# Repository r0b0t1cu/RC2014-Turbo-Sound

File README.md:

# RC2014 Turbo Sound

An original dual AY/YM TurboSound board for RC bus systems and compatible Z80 computers. The design combines two AY-compatible sound chips, a stereo audio output, selectable address decoding, and clock-source/divider options.

The schematic and PCB were developed for this project. The compact DIP layout was designed to fit within the RC bus width while keeping the board height acceptable.

## Features

- Two AY-3-8910 or YM2149-compatible sound chips.
- TurboSound chip selection through the board's `$F8` / `$F9` soft-select commands.
- Selectable MSX-style 8-bit I/O and ZX Spectrum-style 16-bit I/O address decoding.
- Onboard oscillator or RC bus clock, with selectable clock division.
- Stereo audio output.
- Two-row J1 RC bus connector footprint; one row provides the electrical connection and the additional row supports RC bus fit and mechanical stability.

---

*Click the image above to watch the project demonstration on YouTube.*

## Compatibility

Designed for RC bus / RC2014 systems, including compatible SC7xx RCBus computers. It can also be used with a ZX Spectrum through an appropriate adapter and matching software configuration.

TSPLAYER is the companion CP/M/RomWBW PT3 player: [r0b0t1cu/TSPLAYER](https://github.com/r0b0t1cu/TSPLAYER). TSPLAYER controls the two AY chips through the board's shared AY port pair and `$F8` / `$F9` selection commands. Its eight-LED level display uses the separate RCBus Digital I/O module at port 0.

## Design and documentation files

| File | Description |
| --- | --- |
| [`RC2014-Turbo-Sound-KiCad/`](RC2014-Turbo-Sound-KiCad/) | Editable KiCad schematic, PCB, project, and custom RC bus footprints |
| [`docs/schematic.pdf`](docs/schematic.pdf) | Schematic PDF |
| [`docs/images/turbosound-board-photo.jpg`](docs/images/turbosound-board-photo.jpg) | Photograph of the assembled board |
| [`docs/images/board-top.png`](docs/images/board-top.png) | Top-side PCB render |
| [`docs/images/board-bottom.png`](docs/images/board-bottom.png) | Bottom-side PCB render and silkscreen jumper legend |
| [`docs/ibom.html`](docs/ibom.html) | Interactive bill of materials |
| [`docs/JUMPER_SETTINGS.md`](docs/JUMPER_SETTINGS.md) | Address, mode, clock, and connector notes |

## Fabrication files

Generated files are in [`production/2026-11-07-21-17-36/`](production/2026-11-07-21-17-36/): [BOM](production/2026-11-07-21-17-36/RC2014-Turbo-Sound.kicad_pcb_bom.csv), [component positions](production/2026-11-07-21-17-36/RC2014-Turbo-Sound.kicad_pcb_positions.csv), [IPC netlist](production/2026-11-07-21-17-36/RC2014-Turbo-Sound.kicad_pcb_netlist.ipc), and [Gerber archive](production/2026-11-07-21-17-36/RC2014-Turbo-Sound.kicad_pcb_gerber.zip).

If you enjoy my projects and would like to support my work, you can do so through PCBWay. You can also order the PCBs for this project directly from the link below. Every bit of support is appreciated!

<p>
  
</p>

## Design inspiration and credits

The design was inspired by the TurboSound interface concepts in [KTS](https://github.com/konkotgit/KTS) and the AY/YM sound-board work in [electrified/rc2014-ym2149](https://github.com/electrified/rc2014-ym2149). Those projects remain the work of their respective authors. The schematic implementation and PCB layout in this repository were developed for this board.

## License

Hardware design files are released under the **CERN Open Hardware Licence Version 2 – Permissive (CERN-OHL-P-2.0)**. See [LICENSE](LICENSE). The license permits use, modification, manufacture, and sale, subject to its terms and notices.

Copyright © 2025-2026 r0b0t1cu.

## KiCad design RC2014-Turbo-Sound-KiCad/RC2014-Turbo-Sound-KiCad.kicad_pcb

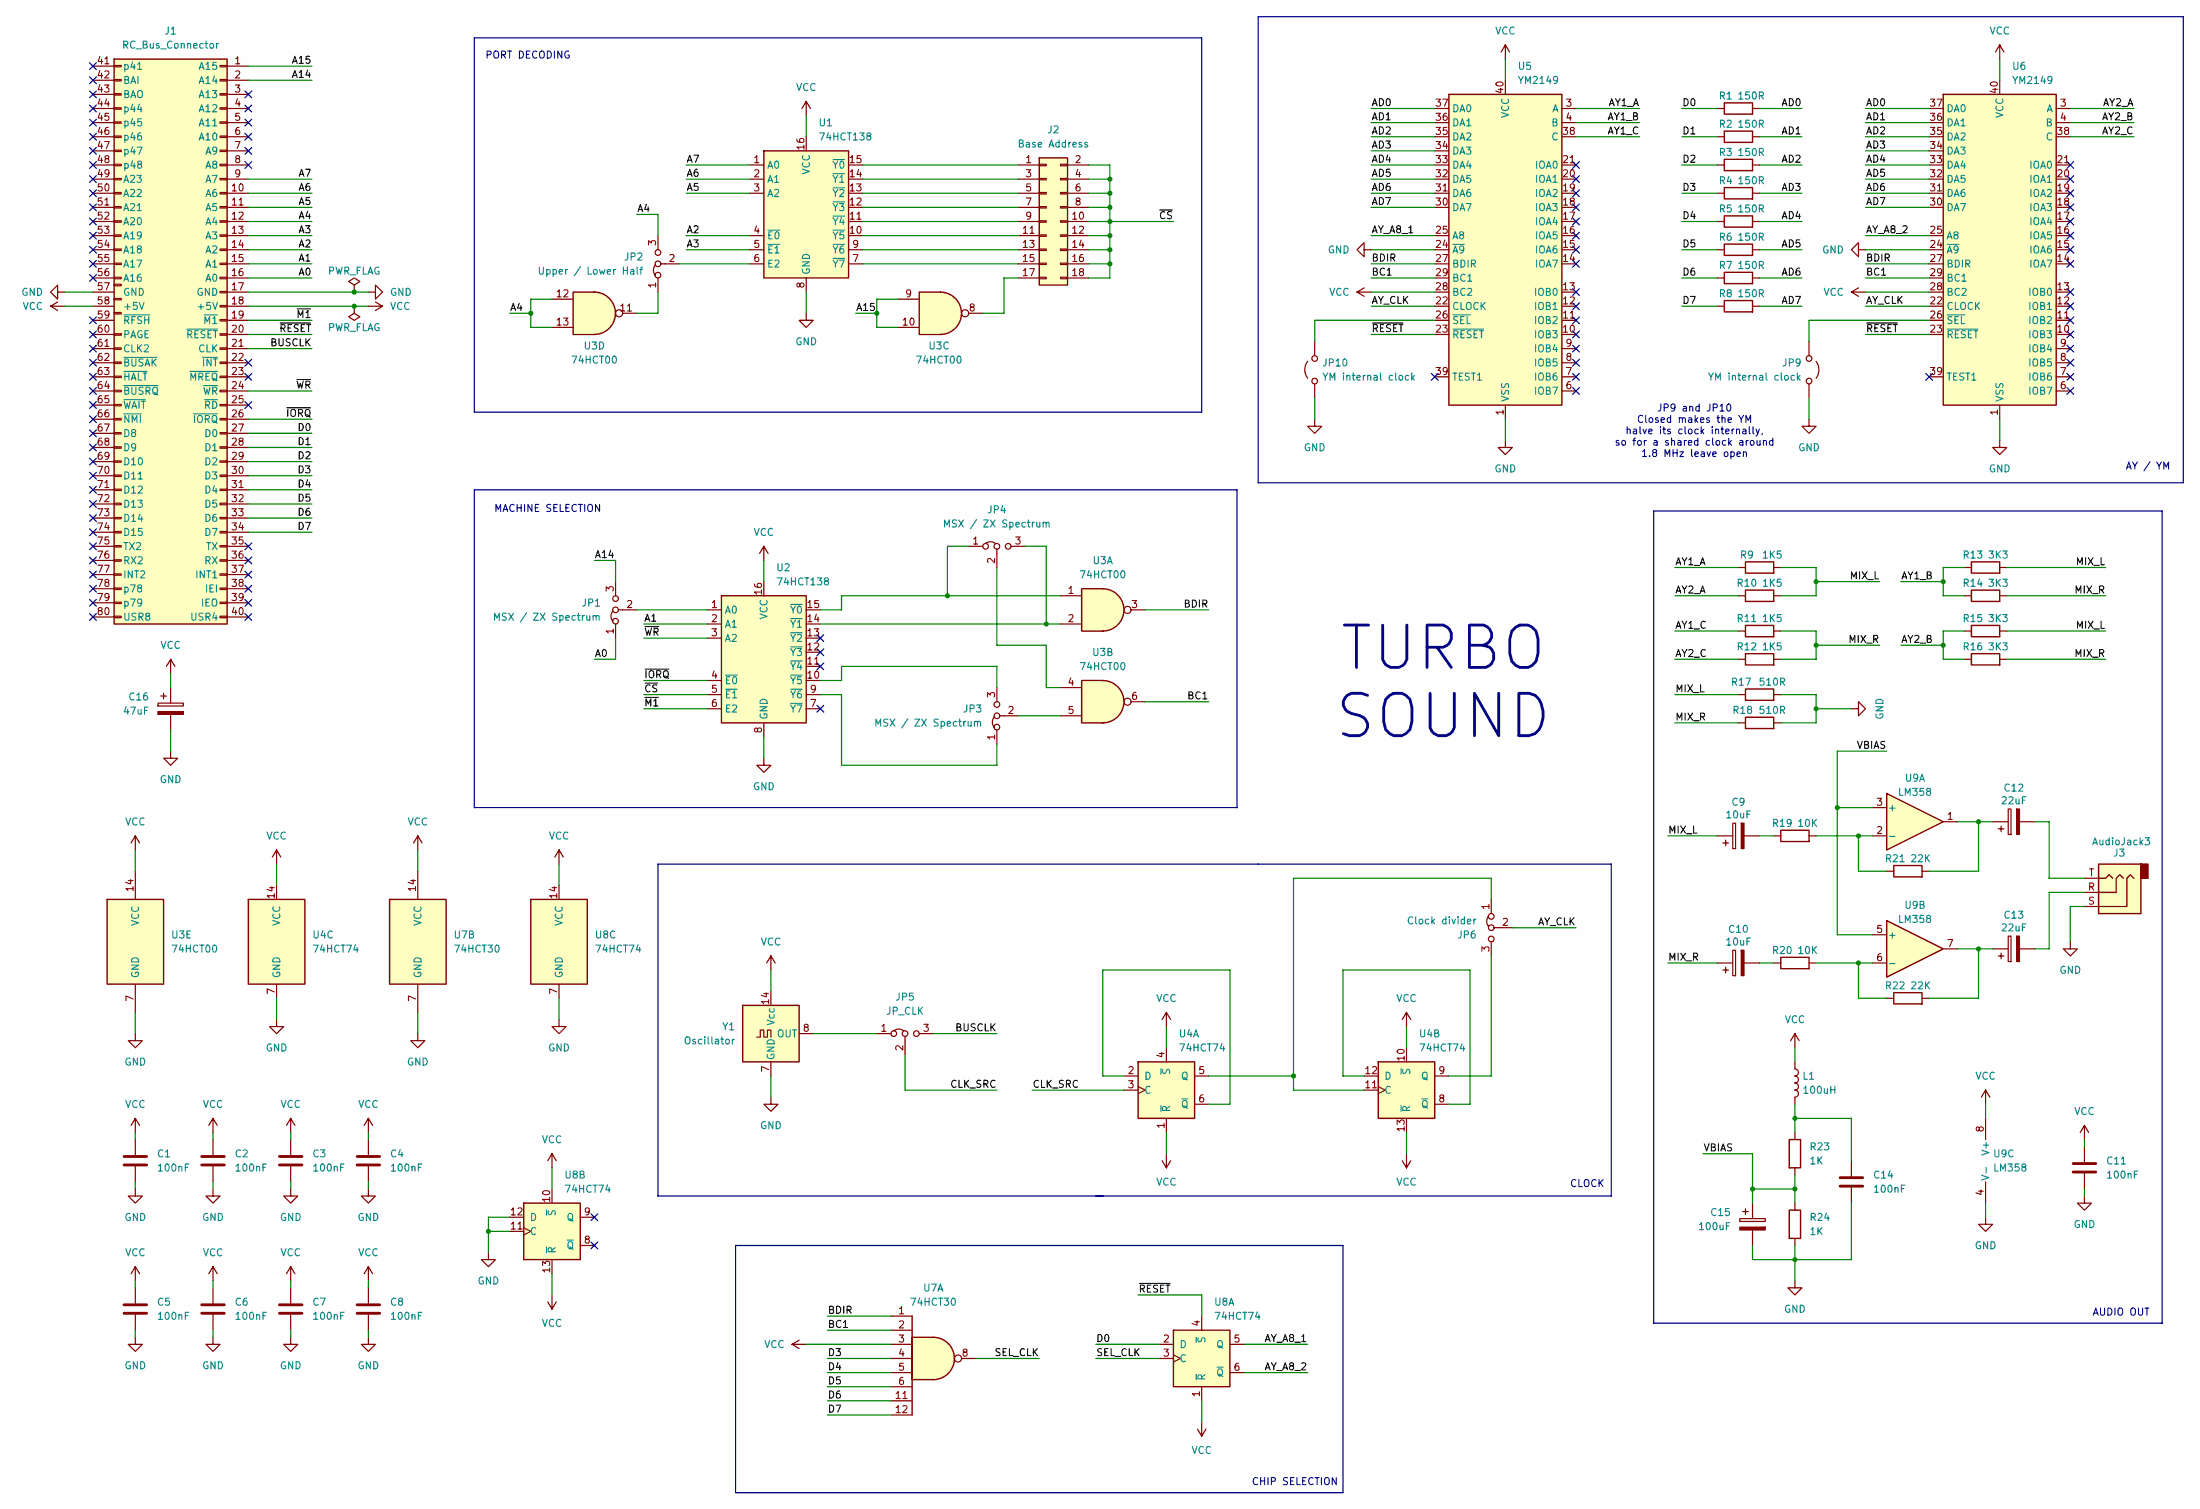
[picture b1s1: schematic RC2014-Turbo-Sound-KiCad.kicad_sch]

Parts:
C1, C2, C3, C4, C5, C6, C7, C8, C11, C14: 100nF; C_Disc_D5.0mm_W2.5mm_P2.50mm
C9, C10: 10uF; CP_Radial_D5.0mm_P2.50mm
C12, C13: 22uF; CP_Radial_D5.0mm_P2.50mm
C15: 100uF; CP_Radial_D5.0mm_P2.50mm
C16: 47uF; CP_Radial_D5.0mm_P2.50mm
J1: RC_Bus_Connector; PinHeader_2x40_P2.54mm_Vertical
J2: Base Address; PinHeader_2x09_P2.54mm_Vertical
J3: AudioJack3; Jack_3.5mm_CUI_SJ1-3525N_Horizontal
JP1, JP3, JP4: MSX / ZX Spectrum; PinHeader_1x03_P2.54mm_Vertical
JP2: Upper / Lower Half; PinHeader_1x03_P2.54mm_Vertical
JP5: JP_CLK; PinHeader_1x03_P2.54mm_Vertical
JP6: Clock divider; PinHeader_1x03_P2.54mm_Vertical
JP9, JP10: YM internal clock; PinHeader_1x02_P2.54mm_Vertical
L1: 100uH; L_Radial_D8.7mm_P5.00mm_Fastron_07HCP
R1, R2, R3, R4, R5, R6, R7, R8: 150R; R_Axial_DIN0207_L6.3mm_D2.5mm_P7.62mm_Horizontal
R9, R10, R11, R12: 1K5; R_Axial_DIN0207_L6.3mm_D2.5mm_P7.62mm_Horizontal
R13, R14, R15, R16: 3K3; R_Axial_DIN0207_L6.3mm_D2.5mm_P7.62mm_Horizontal
R17, R18: 510R; R_Axial_DIN0207_L6.3mm_D2.5mm_P7.62mm_Horizontal
R19, R20: 10K; R_Axial_DIN0207_L6.3mm_D2.5mm_P7.62mm_Horizontal
R21, R22: 22K; R_Axial_DIN0207_L6.3mm_D2.5mm_P7.62mm_Horizontal
R23, R24: 1K; R_Axial_DIN0207_L6.3mm_D2.5mm_P7.62mm_Horizontal
U1, U2: 74HCT138; DIP-16_W7.62mm_Socket_LongPads
U3: 74HCT00; DIP-14_W7.62mm_Socket_LongPads
U4, U8: 74HCT74; DIP-14_W7.62mm_Socket_LongPads
U5, U6: YM2149; DIP-40_W15.24mm_Socket_LongPads
U7: 74HCT30; DIP-14_W7.62mm_Socket_LongPads
U9: LM358; DIP-8_W7.62mm_Socket_LongPads
Y1: Oscillator; DIP-14_W7.62mm_Socket_LongPads

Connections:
/A0: J1.16 (A0), JP1.1 (A)
/A1: J1.15 (A1), U2.2 (A1)
/A2: J1.14 (A2), U1.4 (~E0)
/A3: J1.13 (A3), U1.5 (~E1)
/A4: J1.12 (A4), JP2.3 (B), U3.12, U3.13
/A5: J1.11 (A5), U1.3 (A2)
/A6: J1.10 (A6), U1.2 (A1)
/A7: J1.9 (A7), U1.1 (A0)
/A14: J1.2 (A14), JP1.3 (B)
/A15: J1.1 (A15), U3.9, U3.10
/AD0: R1.2, U5.37 (DA0), U6.37 (DA0)
/AD1: R2.2, U5.36 (DA1), U6.36 (DA1)
/AD2: R3.2, U5.35 (DA2), U6.35 (DA2)
/AD3: R4.2, U5.34 (DA3), U6.34 (DA3)
/AD4: R5.2, U5.33 (DA4), U6.33 (DA4)
/AD5: R6.2, U5.32 (DA5), U6.32 (DA5)
/AD6: R7.2, U5.31 (DA6), U6.31 (DA6)
/AD7: R8.2, U5.30 (DA7), U6.30 (DA7)
/AY1_A: R9.1, U5.3 (A)
/AY1_B: R13.1, R14.1, U5.4 (B)
/AY1_C: R11.1, U5.38 (C)
/AY2_A: R10.1, U6.3 (A)
/AY2_B: R15.1, R16.1, U6.4 (B)
/AY2_C: R12.1, U6.38 (C)
/AY_A8_1: U5.25 (A8), U8.5 (Q)
/AY_A8_2: U6.25 (A8), U8.6 (~Q)
/AY_CLK: JP6.2 (C), U5.22 (CLOCK), U6.22 (CLOCK)
/BC1: U3.6, U5.29 (BC1), U6.29 (BC1), U7.2
/BDIR: U3.3, U5.27 (BDIR), U6.27 (BDIR), U7.1
/BUSCLK: J1.21 (CLK), JP5.3 (B)
/CLK_SRC: JP5.2 (C), U4.3 (C)
/D0: J1.27 (D0), R1.1, U8.2 (D)
/D1: J1.28 (D1), R2.1
/D2: J1.29 (D2), R3.1
/D3: J1.30 (D3), R4.1, U7.4
/D4: J1.31 (D4), R5.1, U7.5
/D5: J1.32 (D5), R6.1, U7.6
/D6: J1.33 (D6), R7.1, U7.11
/D7: J1.34 (D7), R8.1, U7.12
/MIX_L: C9.1, R9.2, R10.2, R13.2, R15.2, R17.1
/MIX_R: C10.1, R11.2, R12.2, R14.2, R16.2, R18.1
/SEL_CLK: U7.8, U8.3 (C)
/VBIAS: C15.1, R23.2, R24.1, U9.3 (+), U9.5 (+)
/~CS: J2.2, J2.4, J2.6, J2.8, J2.10, J2.12, J2.14, J2.16, J2.18, U2.5 (~E1)
/~IORQ: J1.26 (~IORQ), U2.4 (~E0)
/~M1: J1.19 (~M1), U2.6 (E2)
/~RESET: J1.20 (~RESET), U5.23 (~RESET), U6.23 (~RESET), U8.4 (~S)
/~WR: J1.24 (~WR), U2.3 (A2)
GND: C1.2, C2.2, C3.2, C4.2, C5.2, C6.2, C7.2, C8.2, C11.2, C14.2, C15.2, C16.2, J1.17 (GND), J1.57 (GND), J3.S, JP9.1 (A), JP10.1 (A), R17.2, R18.2, R24.2, U1.8 (GND), U2.8 (GND), U3.7 (GND), U4.7 (GND), U5.1 (VSS), U5.24 (~A9), U6.1 (VSS), U6.24 (~A9), U7.7 (GND), U8.7 (GND), U8.11 (C), U8.12 (D), U9.4 (V-), Y1.4, Y1.7 (GND)
unnamed: C9.2, R19.1
unnamed: C10.2, R20.1
unnamed: C12.1, R21.2, U9.1
unnamed: C12.2, J3.T, J3.TN
unnamed: C13.1, R22.2, U9.7
unnamed: C13.2, J3.R, J3.RN
unnamed: C14.1, L1.2, R23.1
unnamed: J2.1, U1.15 (~Y0)
unnamed: J2.3, U1.14 (~Y1)
unnamed: J2.5, U1.13 (~Y2)
unnamed: J2.7, U1.12 (~Y3)
unnamed: J2.9, U1.11 (~Y4)
unnamed: J2.11, U1.10 (~Y5)
unnamed: J2.13, U1.9 (~Y6)
unnamed: J2.15, U1.7 (~Y7)
unnamed: J2.17, U3.8
unnamed: JP1.2 (C), U2.1 (A0)
unnamed: JP2.1 (A), U3.11
unnamed: JP2.2 (C), U1.6 (E2)
unnamed: JP3.1 (A), U2.9 (~Y6)
unnamed: JP3.3 (B), U2.10 (~Y5)
unnamed: JP3.2 (C), U3.5
unnamed: JP4.1 (A), U2.15 (~Y0), U3.1
unnamed: JP4.3 (B), U2.14 (~Y1), U3.2
unnamed: JP4.2 (C), U3.4
unnamed: JP5.1 (A), Y1.8 (OUT), Y1.11
unnamed: JP6.1 (A), U4.5 (Q), U4.11 (C)
unnamed: JP6.3 (B), U4.9 (Q)
unnamed: JP9.2 (B), U6.26 (~SEL)
unnamed: JP10.2 (B), U5.26 (~SEL)
unnamed: U4.2 (D), U4.6 (~Q)
unnamed: U4.8 (~Q), U4.12 (D)
unnamed: R19.2, R21.1, U9.2 (-)
unnamed: R20.2, R22.1, U9.6 (-)
VCC: C1.1, C2.1, C3.1, C4.1, C5.1, C6.1, C7.1, C8.1, C11.1, C16.1, J1.18 (+5V), J1.58 (+5V), L1.1, U1.16 (VCC), U2.16 (VCC), U3.14 (VCC), U4.1 (~R), U4.4 (~S), U4.10 (~S), U4.13 (~R), U4.14 (VCC), U5.28 (BC2), U5.40 (VCC), U6.28 (BC2), U6.40 (VCC), U7.3, U7.14 (VCC), U8.1 (~R), U8.10 (~S), U8.13 (~R), U8.14 (VCC), U9.8 (V+), Y1.14 (Vcc)

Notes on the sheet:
AUDIO OUT
AY / YM
PORT DECODING
CHIP SELECTION
TURBO SOUND
JP9 and JP10 Closed makes the YM halve its clock internally, so for a shared clock around 1.8 MHz leave open
MACHINE SELECTION
CLOCK

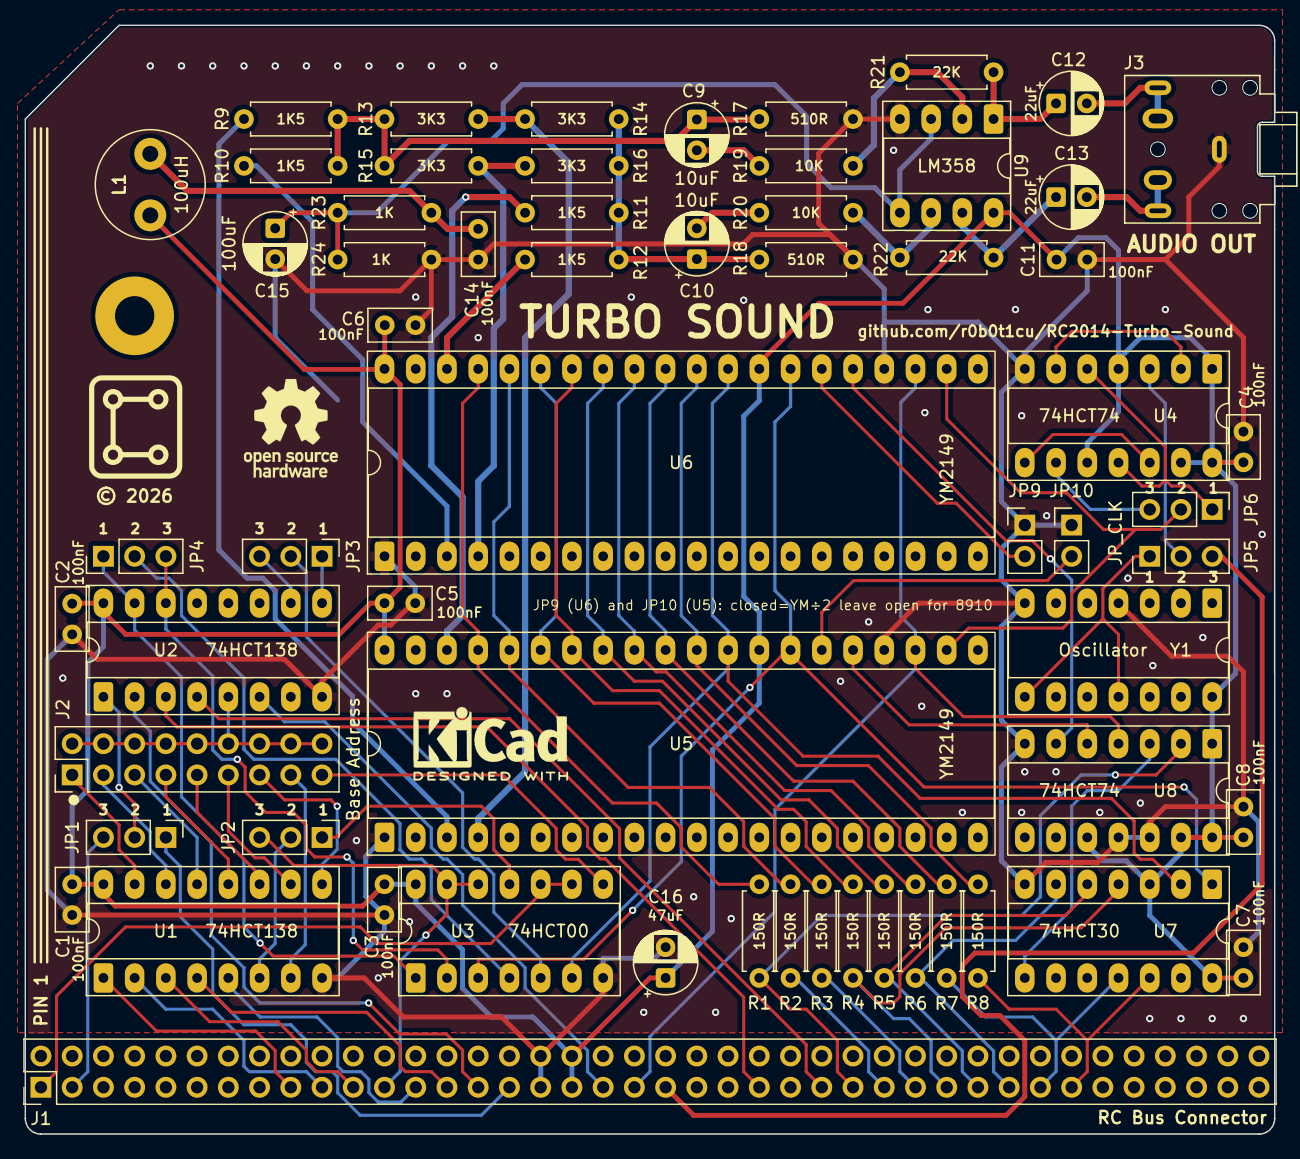
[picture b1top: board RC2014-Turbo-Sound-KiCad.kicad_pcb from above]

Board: 2 copper layers, 101.6 x 90.2 mm, 62 parts (0 on the bottom side), 84 nets.

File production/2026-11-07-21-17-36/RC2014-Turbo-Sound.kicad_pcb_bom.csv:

Designator,Quantity,Value,Footprint,Package,MPN,DNP,Mount_Type,Description,KiLib_Generator
"C1, C11, C14, C2, C3, C4, C5, C6, C7, C8",10,100nF,C_Disc_D5.0mm_W2.5mm_P2.50mm,,,,tht,Unpolarized capacitor,capacitor/THT/other
"C10, C9",2,10uF,CP_Radial_D5.0mm_P2.50mm,,,,tht,Polarized capacitor,capacitor/THT/other
"C12, C13",2,22uF,CP_Radial_D5.0mm_P2.50mm,,,,tht,Polarized capacitor,capacitor/THT/other
C15,1,100uF,CP_Radial_D5.0mm_P2.50mm,,,,tht,Polarized capacitor,capacitor/THT/other
C16,1,47uF,CP_Radial_D5.0mm_P2.50mm,,,,tht,Polarized capacitor,capacitor/THT/other
J1,1,RC_Bus_Connector,PinHeader_2x40_P2.54mm_Vertical,,,,tht,Generic RCBus connector,connector/pin_header_socket
J2,1,Base Address,PinHeader_2x09_P2.54mm_Vertical,,,,tht,"Generic connector, double row, 02x09, odd/even pin numbering scheme (row 1 odd numbers, row 2 even numbers), script generated (kicad-library-utils/schlib/autogen/connector/)",connector/pin_header_socket
J3,1,AudioJack3,Jack_3.5mm_CUI_SJ1-3525N_Horizontal,,,,tht,"Audio Jack, 3 Poles (Stereo / TRS)",
"JP10, JP9",2,YM internal clock,PinHeader_1x02_P2.54mm_Vertical,,,,tht,"Jumper, 2-pole, open",connector/pin_header_socket
L1,1,100uH,L_Radial_D8.7mm_P5.00mm_Fastron_07HCP,,,,tht,Inductor,choke_THT
"R1, R2, R3, R4, R5, R6, R7, R8",8,150R,R_Axial_DIN0207_L6.3mm_D2.5mm_P7.62mm_Horizontal,,,,tht,Resistor,resistor/THT
"R10, R11, R12, R9",4,1K5,R_Axial_DIN0207_L6.3mm_D2.5mm_P7.62mm_Horizontal,,,,tht,Resistor,resistor/THT
"R13, R14, R15, R16",4,3K3,R_Axial_DIN0207_L6.3mm_D2.5mm_P7.62mm_Horizontal,,,,tht,Resistor,resistor/THT
"R17, R18",2,510R,R_Axial_DIN0207_L6.3mm_D2.5mm_P7.62mm_Horizontal,,,,tht,Resistor,resistor/THT
"R19, R20",2,10K,R_Axial_DIN0207_L6.3mm_D2.5mm_P7.62mm_Horizontal,,,,tht,Resistor,resistor/THT
"R21, R22",2,22K,R_Axial_DIN0207_L6.3mm_D2.5mm_P7.62mm_Horizontal,,,,tht,Resistor,resistor/THT
"R23, R24",2,1K,R_Axial_DIN0207_L6.3mm_D2.5mm_P7.62mm_Horizontal,,,,tht,Resistor,resistor/THT
"U1, U2",2,74HCT138,DIP-16_W7.62mm_Socket_LongPads,,,,tht,"3-to-8 line decoder/multiplexer inverting, DIP-16/SOIC-16/SSOP-16",package/DIP/legacy
U3,1,74HCT00,DIP-14_W7.62mm_Socket_LongPads,,,,tht,quad 2-input NAND gate,package/DIP/legacy
"U4, U8",2,74HCT74,DIP-14_W7.62mm_Socket_LongPads,,,,tht,"Dual D Flip-flop, Set & Reset",package/DIP/legacy
"U5, U6",2,YM2149,DIP-40_W15.24mm_Socket_LongPads,,,,tht,"Software-Controlled Sound Generator, DIP-40",package/DIP/legacy
U7,1,74HCT30,DIP-14_W7.62mm_Socket_LongPads,,,,tht,8-input NAND,package/DIP/legacy
U9,1,LM358,DIP-8_W7.62mm_Socket_LongPads,,,,tht,"Low-Power, Dual Operational Amplifiers, DIP-8/SOIC-8/TO-99-8",package/DIP/legacy
Y1,1,Oscillator,DIP-14_W7.62mm_Socket_LongPads,,,,tht,"HCMOS Crystal Clock Oscillator, DIP14-style metal package",package/DIP/legacy

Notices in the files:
RC2014-Turbo-Sound-KiCad/RC2014-Turbo-Sound-KiCad.kicad_pcb:
© 2026
